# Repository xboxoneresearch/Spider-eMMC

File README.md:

# Spider-eMMC
KiCad 7.0 projects for SpiderUnifiedBoard and SpiderCarrierBoard, Xbox One eMMC replacement and repair boards.

_Note_: these projects are uncompleted and provided AS-IS. 

## Why?
Lack of time, resources and motivation to finish the project. Passing off the torch.
This was meant to be a complete solution to repair Xbox One consoles with damaged / degraded eMMCs. The main board would be put in the console (with minimal soldering needed), and then you could swap different eMMC modules.

- The form factor of the main board is for all Xbox One PHAT variations (Durango/Graybull, Carmel, Silverton) **and you can reuse it directly!** (this is the Edge Cuts layer in KiCad)
- The form factor is not adapted for Xbox One S nor Xbox One X

## Theory of Operation
- Xbox One's southbridge uses the whole 8-bit bus to connect to the eMMC, so it cannot be replaced by cheaper and easier eMMC compatible memories (i.e.: microSD cards)
- To minimize desoldering of ICs: You would cut the traces from the original eMMC in the board to the southbrige.
- Then you would solder this board and connect the new data and control lines, at which point the southbridge will start communicating with the new and fresh eMMC on the Spider board (or in the carrier board)

## Spider Unified Board
First prototype eMMC replacement board. This board did not feature a removable eMMC yet.
This board must be modified to replace the eMMC with a socket, where you can plug the Spider Carrier Board (see below)

## Spider Carrier Board
An attachable PCB carrying an eMMC memory. This board was meant to be plugged into the main Spider board, having a B2B socket in it.

## Credits
- TorusHyperV: Original design and iteration (and killing several consoles for science)
- XBR Team: invaluable feedback and idea of the removable eMMC board
- Betatesters: for their invaluable help and courage to test early board prototypes
  - SheezNeez
  - Wolf
  - ModzvilleUSA
  - mc_quezada
  - Heathenhkr

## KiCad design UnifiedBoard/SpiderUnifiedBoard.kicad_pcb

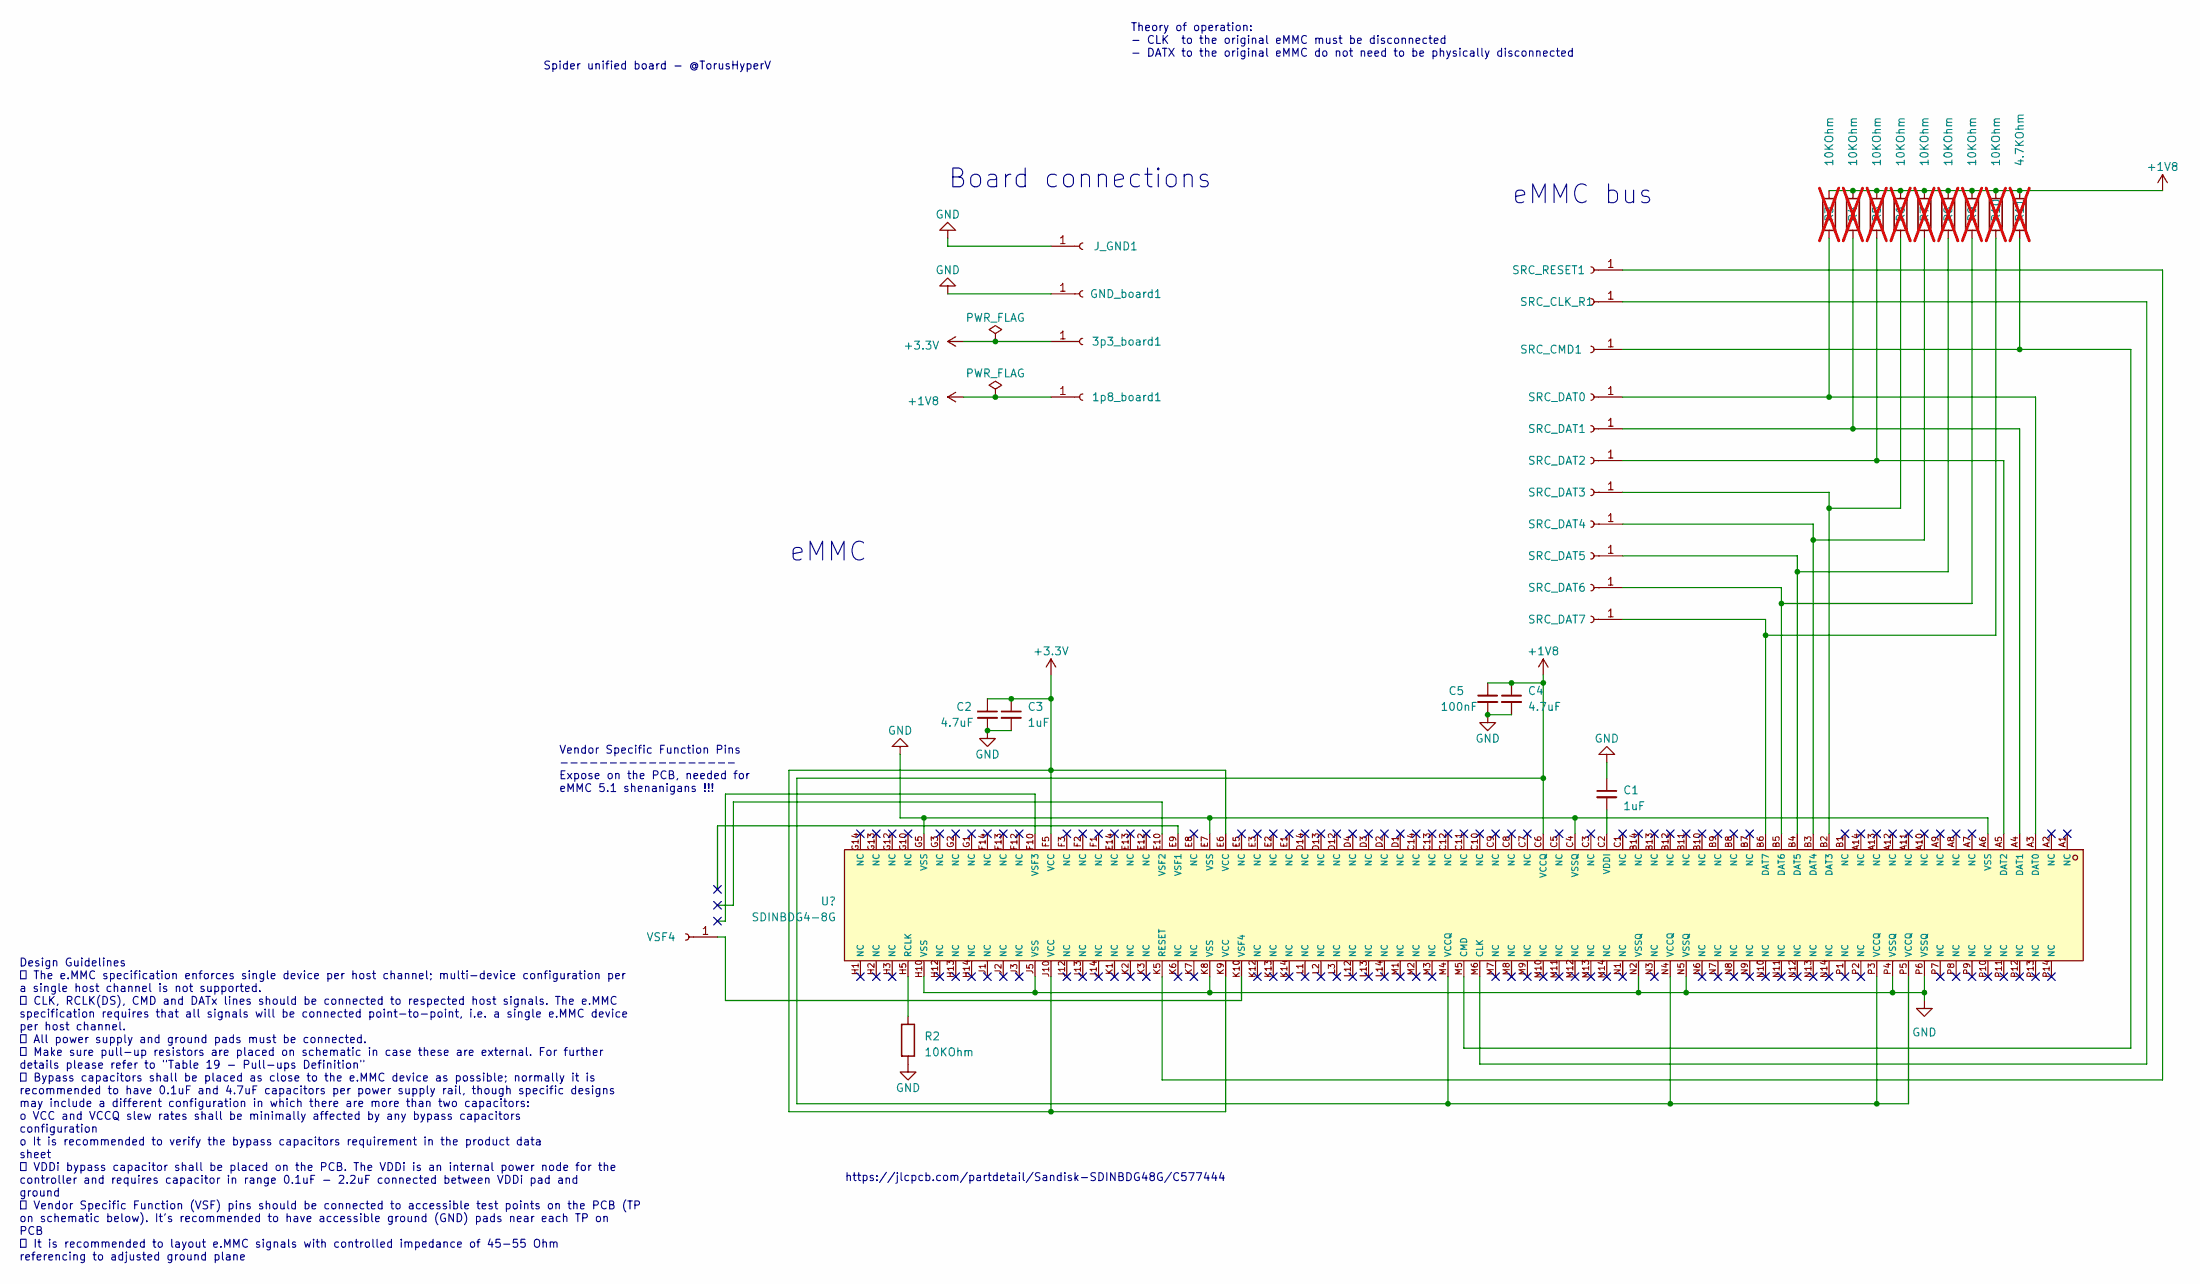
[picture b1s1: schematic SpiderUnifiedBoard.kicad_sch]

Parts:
1p8_board1, 3p3_board1: Conn_01x01_Female; TestPoint_Pad_D2.0mm
C1, C3: 1uF; C_0402_1005Metric
C2, C4: 4.7uF; C_0402_1005Metric
C5: 100nF; C_0402_1005Metric
GND_board1: Conn_01x01_Female; TestPoint_Pad_D2.0mm
J_GND1: Conn_01x01_Female; TestPoint_Pad_1.0x1.0mm
R2: 10KOhm; R_0402_1005Metric
R3, R4, R5, R6, R7, R8, R9, R10: 10KOhm; R_0402_1005Metric; not fitted
R11: 4.7KOhm; R_0402_1005Metric; not fitted
SRC_CLK_R1: Conn_01x01_Female; TestPoint_Pad_1.0x1.0mm
SRC_CMD1: Conn_01x01_Female; TestPoint_Pad_D1.0mm
SRC_DAT0, SRC_DAT1, SRC_DAT2, SRC_DAT3, SRC_DAT4, SRC_DAT5, SRC_DAT6, SRC_DAT7: Conn_01x01_Female; TestPoint_Pad_D1.0mm
SRC_RESET1: Conn_01x01_Female; TestPoint_Pad_D1.0mm
VSF4: Conn_01x01_Female; TestPoint_Pad_D1.0mm

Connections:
+1V8: 1p8_board1.1, C4.1, C5.1, R3.1, R4.1, R5.1, R6.1, R7.1, R8.1, R9.1, R10.1, R11.1; also elsewhere on the board
+3.3V: 3p3_board1.1, C2.1, C3.1; also elsewhere on the board
GND: C1.1, C2.2, C3.2, C4.2, C5.2, GND_board1.1, J_GND1.1, R2.2; also elsewhere on the board
unnamed 3: SRC_CLK_R1.1; also elsewhere on the board
unnamed 4: R11.2, SRC_CMD1.1; also elsewhere on the board
unnamed 5: R3.2, SRC_DAT0.1; also elsewhere on the board
unnamed 6: R4.2, SRC_DAT1.1; also elsewhere on the board
unnamed 7: R5.2, SRC_DAT2.1; also elsewhere on the board
unnamed 8: R6.2, SRC_DAT3.1; also elsewhere on the board
unnamed 9: R7.2, SRC_DAT4.1; also elsewhere on the board
unnamed 10: R8.2, SRC_DAT5.1; also elsewhere on the board
unnamed 11: R9.2, SRC_DAT6.1; also elsewhere on the board
unnamed 12: R10.2, SRC_DAT7.1; also elsewhere on the board
unnamed 13: SRC_RESET1.1; also elsewhere on the board
unnamed 14: R2.1; also elsewhere on the board
unnamed 15: C1.2; also elsewhere on the board
unnamed 16: VSF4.1; also elsewhere on the board

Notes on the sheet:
Spider unified board - @TorusHyperV
eMMC
eMMC bus
Design Guidelines  The e.MMC specification enforces single device per host channel; multi-device configuration per a single host channel is not supported.  CLK, RCLK(DS), CMD and DATx lines should be connected to respected host signals. The e.MMC specification requires that all signals will be co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
Vendor Specific Function Pins ------------------ Expose on the PCB, needed for eMMC 5.1 shenanigans !!!
https://jlcpcb.com/partdetail/Sandisk-SDINBDG48G/C577444
Board connections
Theory of operation: - CLK to the original eMMC must be disconnected - DATX to the original eMMC do not need to be physically disconnected

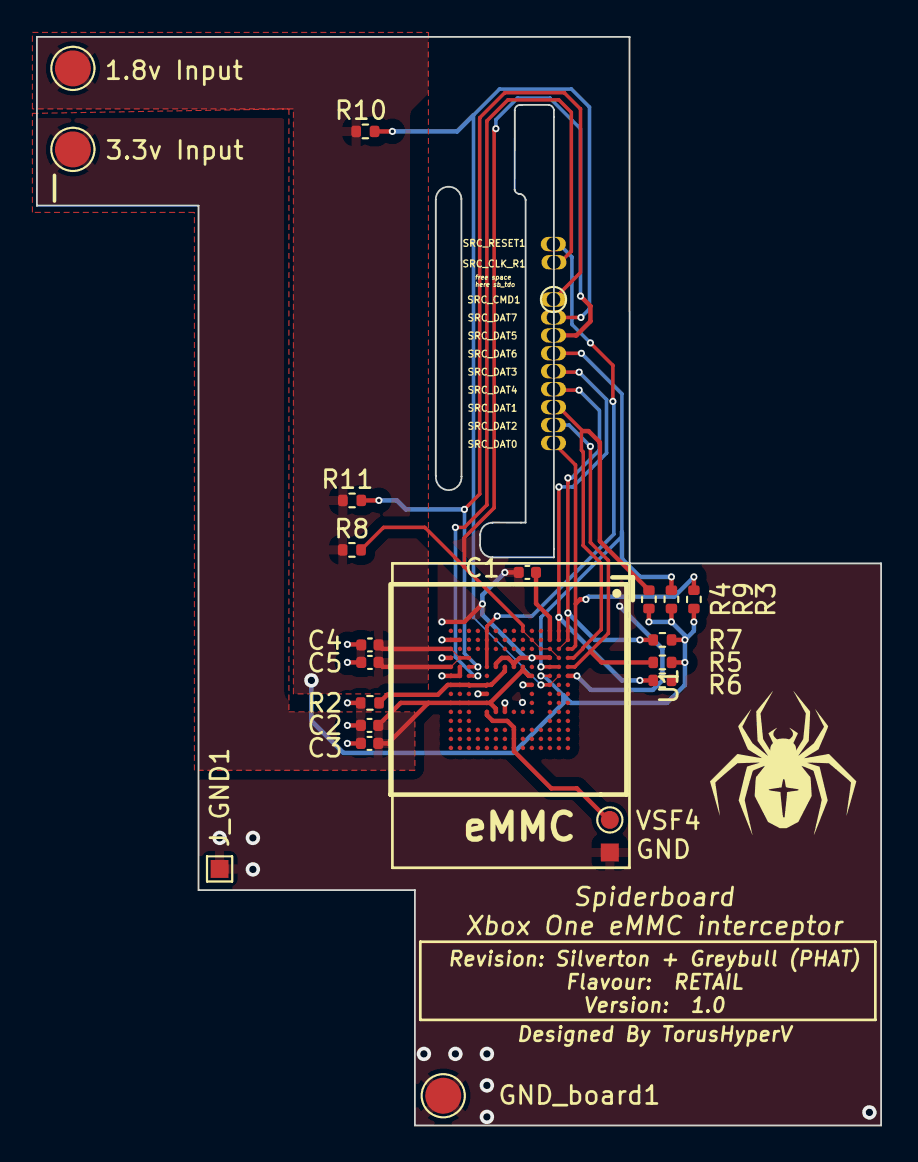
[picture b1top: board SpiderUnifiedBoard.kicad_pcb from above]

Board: 2 copper layers, 46.9 x 60.5 mm, 32 parts (0 on the bottom side), 17 nets.

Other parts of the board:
1.8v Input, 3.3v Input: Conn_01x01_Female; TestPoint_Pad_D2.0mm
U1: SDINBDG4-8G; FBGA-153_L13.0-W11.5-P0.50_KLMAG1JETD-B041

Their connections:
+1V8: 1.8v Input.1, U1.C6 (VCCQ), U1.M4 (VCCQ), U1.N4 (VCCQ), U1.P3 (VCCQ), U1.P5 (VCCQ); also elsewhere on the board
+3.3V: 3.3v Input.1, U1.E6 (VCC), U1.F5 (VCC), U1.J10 (VCC), U1.K9 (VCC); also elsewhere on the board
GND: U1.A6 (VSS), U1.C4 (VSSQ), U1.E7 (VSS), U1.G5 (VSS), U1.H10 (VSS), U1.J5 (VSS), U1.K8 (VSS), U1.N2 (VSSQ), U1.N5 (VSSQ), U1.P4 (VSSQ), U1.P6 (VSSQ); also elsewhere on the board
unnamed 3: U1.M6 (CLK); also elsewhere on the board
unnamed 4: U1.M5 (CMD); also elsewhere on the board
unnamed 5: U1.A3 (DAT0); also elsewhere on the board
unnamed 6: U1.A4 (DAT1); also elsewhere on the board
unnamed 7: U1.A5 (DAT2); also elsewhere on the board
unnamed 8: U1.B2 (DAT3); also elsewhere on the board
unnamed 9: U1.B3 (DAT4); also elsewhere on the board
unnamed 10: U1.B4 (DAT5), U1.C3 (NC), U1.D3 (NC), U1.E2 (NC), U1.F1 (NC); also elsewhere on the board
unnamed 11: U1.B5 (DAT6); also elsewhere on the board
unnamed 12: U1.B6 (DAT7); also elsewhere on the board
unnamed 13: U1.K5 (RESET); also elsewhere on the board
unnamed 14: U1.H5 (RCLK); also elsewhere on the board
unnamed 15: U1.C2 (VDDI); also elsewhere on the board
unnamed 16: U1.K10 (VSF4); also elsewhere on the board

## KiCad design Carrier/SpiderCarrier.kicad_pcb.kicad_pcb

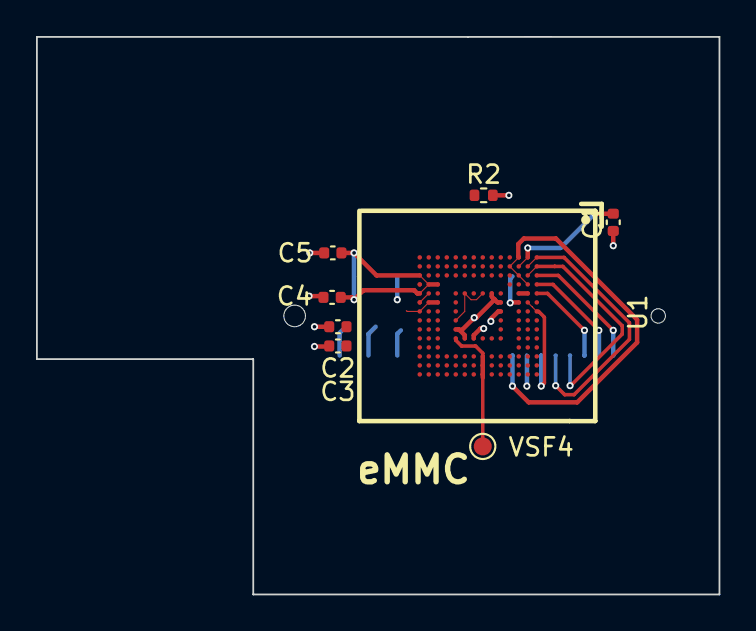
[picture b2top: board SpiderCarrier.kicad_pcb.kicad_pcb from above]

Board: 2 copper layers, 37.9 x 31.0 mm, 9 parts (1 on the bottom side), 17 nets.

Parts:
C1, C3: 1uF; C_0402_1005Metric
C2, C4: 4.7uF; C_0402_1005Metric
C5: 100nF; C_0402_1005Metric
R2: 10KOhm; R_0402_1005Metric
U1: SDINBDG4-8G; FBGA-153_L13.0-W11.5-P0.50_KLMAG1JETD-B041
U4: 61082-041400LF; CONN-SMD_61082-041400LF
VSF4: Conn_01x01_Female; TestPoint_Pad_D1.0mm

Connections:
+1V8: C4.1, C5.1, U1.C6 (VCCQ), U1.M4 (VCCQ), U1.N4 (VCCQ), U1.P3 (VCCQ), U1.P5 (VCCQ), U4.3, U4.25
+3.3V: C2.1, C3.1, U1.E6 (VCC), U1.F5 (VCC), U1.J10 (VCC), U1.K9 (VCC), U4.9
GND: C1.1, C2.2, C3.2, C4.2, C5.2, R2.2, U1.A6 (VSS), U1.C4 (VSSQ), U1.E7 (VSS), U1.G5 (VSS), U1.H10 (VSS), U1.J5 (VSS), U1.K8 (VSS), U1.N2 (VSSQ), U1.N5 (VSSQ), U1.P4 (VSSQ), U1.P6 (VSSQ), U4.1, U4.17, U4.21, U4.39
unnamed: U1.M6 (CLK), U4.6
unnamed: U1.M5 (CMD), U4.10
unnamed: U1.A3 (DAT0), U4.40
unnamed: U1.A4 (DAT1), U4.38
unnamed: U1.A5 (DAT2), U4.36
unnamed: U1.B2 (DAT3), U4.32
unnamed: U1.B3 (DAT4), U4.34
unnamed: U1.B4 (DAT5), U1.C1 (NC), U4.26
unnamed: U1.B5 (DAT6), U1.C5 (NC), U4.28
unnamed: U1.B6 (DAT7), U4.30
unnamed: R2.1, U1.H5 (RCLK)
unnamed: U1.K5 (RESET), U4.2
unnamed: C1.2, U1.B1 (NC), U1.C2 (VDDI)
unnamed: U1.K10 (VSF4), VSF4.1
